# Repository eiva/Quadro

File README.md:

Quadro
======

Собственно это будет клон ардупилота для квадрика.
BOM и прочее будет позднее.
Пока все это теория, т.к. железа у меня нет...

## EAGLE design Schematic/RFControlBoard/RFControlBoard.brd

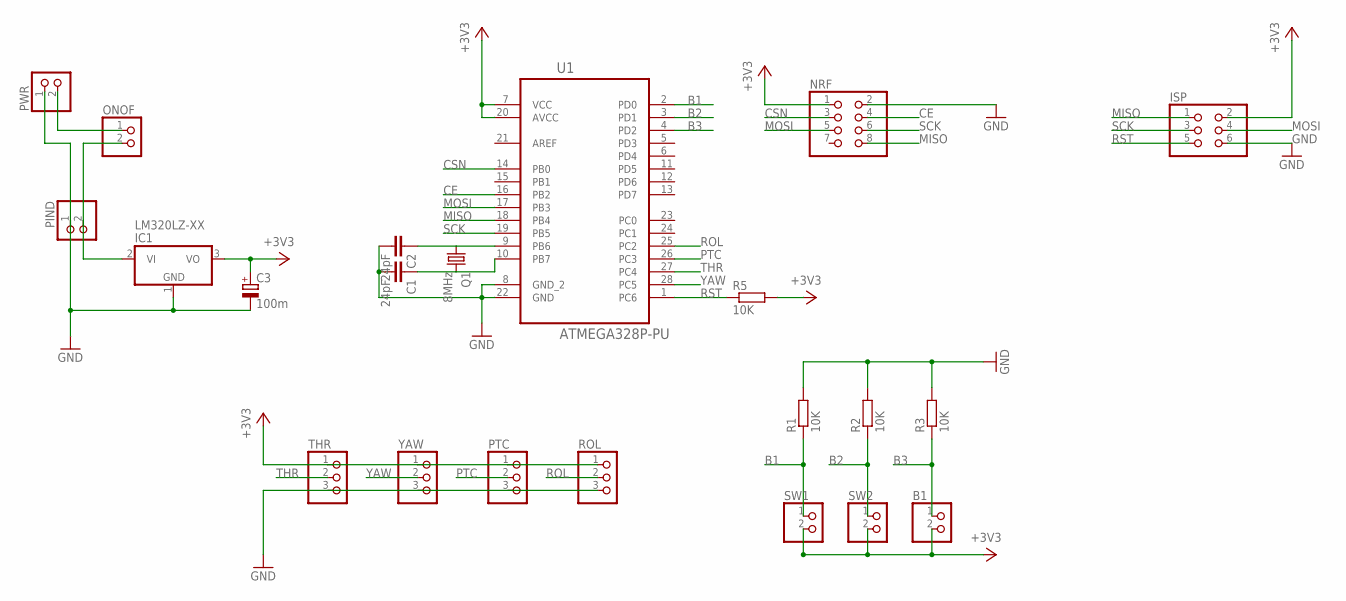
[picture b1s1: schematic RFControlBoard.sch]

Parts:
B1: PINHD-1X2; 1X02
C1, C2: 24pF; C2.5-3
C3: 100m; E2,5-6
IC1: LM320LZ-XX; TO92
ISP: PINHD-2X3; 2X03
NRF: PINHD-2X4; 2X04
ONOF: PINHD-1X2; 1X02
PIND: PINHD-1X2; 1X02
PTC: PINHD-1X3; 1X03
PWR: PINHD-1X2; 1X02
Q1: 8MHz; HC49/S
R1, R2, R3: 10K; 0207/10
R5: 10K; 0207/15
ROL: PINHD-1X3; 1X03
SW1, SW2: PINHD-1X2; 1X02
THR: PINHD-1X3; 1X03
U1: ATMEGA328P-PU; DIP254P762X457-28
YAW: PINHD-1X3; 1X03

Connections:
+3V3: B1.2, C3.+, IC1.3 (VO), ISP.2, NRF.1, PTC.1, R5.2, ROL.1, SW1.2, SW2.2, THR.1, U1.7 (VCC), U1.20 (AVCC), YAW.1
B1: R1.1, SW1.1, U1.2 (PD0)
B2: R2.1, SW2.1, U1.3 (PD1)
B3: B1.1, R3.1, U1.4 (PD2)
CE: NRF.4, U1.16 (PB2)
CSN: NRF.3, U1.14 (PB0)
GND: C1.2, C2.2, C3.-, IC1.1 (GND), ISP.6, NRF.2, PIND.1, PTC.3, PWR.1, R1.2, R2.2, R3.2, ROL.3, THR.3, U1.8 (GND_2), U1.22 (GND), YAW.3
MISO: ISP.1, NRF.8, U1.18 (PB4)
MOSI: ISP.4, NRF.5, U1.17 (PB3)
unnamed: ONOF.1, PWR.2
unnamed: C2.1, Q1.1, U1.9 (PB6)
unnamed: IC1.2 (VI), ONOF.2, PIND.2
unnamed: C1.1, Q1.2, U1.10 (PB7)
PTC: PTC.2, U1.26 (PC3)
ROL: ROL.2, U1.25 (PC2)
RST: ISP.5, R5.1, U1.1 (PC6)
SCK: ISP.3, NRF.6, U1.19 (PB5)
THR: THR.2, U1.27 (PC4)
YAW: U1.28 (PC5), YAW.2

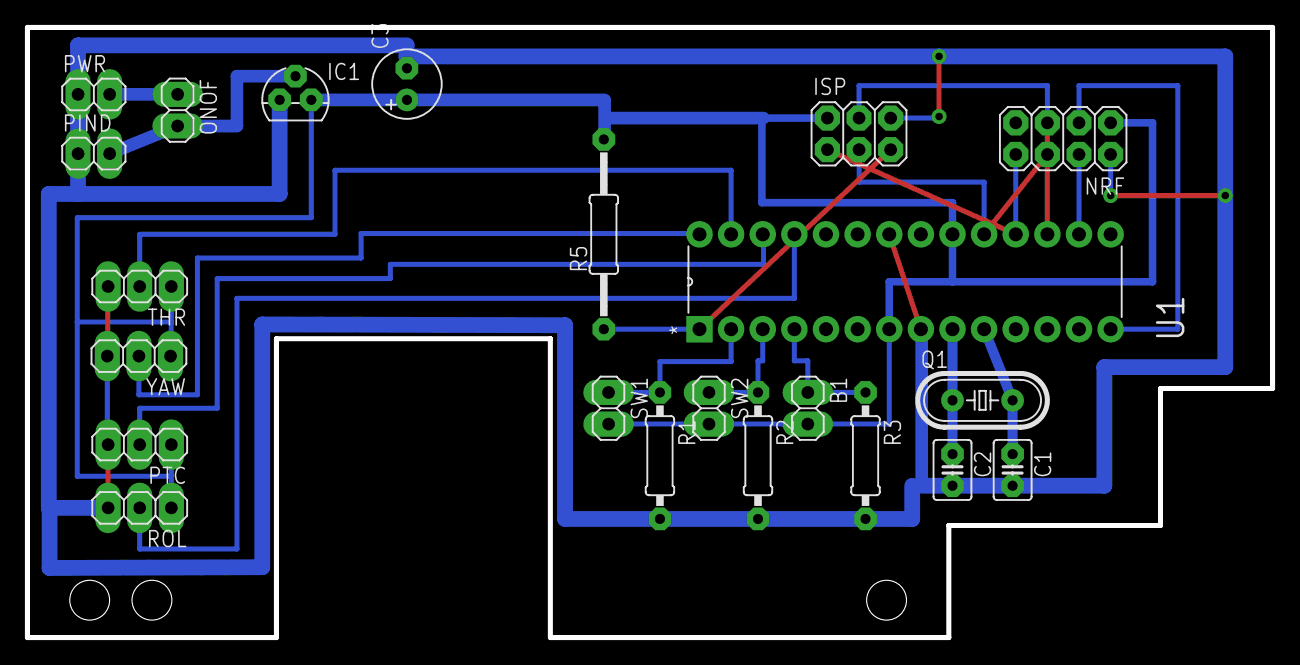
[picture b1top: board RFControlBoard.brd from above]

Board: 2 copper layers, 100.0 x 49.0 mm, 22 parts (0 on the bottom side), 19 nets.

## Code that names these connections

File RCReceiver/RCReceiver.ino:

/**
 * A Mirf example to test the latency between two Ardunio.
 *
 * Pins:
 * Hardware SPI:
 * MISO -> 12
 * MOSI -> 11
 * SCK -> 13
 *
 * Configurable:
 * CE -> 8
 * CSN -> 7
 *
 * Note: To see best case latency comment out all Serial.println
 * statements not displaying the result and load 
 * 'ping_server_interupt' on the server.
 */


#include <SPI.h>
#include <Mirf.h>
#include <nRF24L01.h>
#include <MirfHardwareSpiDriver.h>

#pragma pack(push,1)

struct Packet
{
  uint16_t THR:10;
  uint16_t YAW:10;
  uint16_t PTC:10;
  uint16_t ROL:10;
  uint8_t BT1:1;
  uint8_t BT2:1;
  uint8_t BT3:1;
  uint8_t REST:5;
};

#pragma pack(pop)


//////////////////////CONFIGURATION///////////////////////////////
#define chanel_number 8  //set the number of chanels

#define PPM_FrLen 22500  //set the PPM frame length in microseconds (1ms = 1000µs)
#define PPM_PulseLen 300  //set the pulse length
#define onState 1  //set polarity of the pulses: 1 is positive, 0 is negative
#define sigPin 5  //set PPM signal output pin on the arduino

#define default_servo_value 1500  //set the default servo value
#define  SigMin  1000 // Min value for signal
#define SigMax  2000 // Max value for signal
//////////////////////////////////////////////////////////////////

 
/*this array holds the servo values for the ppm signal
 change theese values in your code (usually servo values move between 1000 and 2000)*/
int ppm[chanel_number];

union PacketSerializer
{
  Packet data;
  uint8_t serialized[6];
};

// Address of reciever.
byte addr[]={0xDB,0xDB,0xDB,0xDB,0xDB};

PacketSerializer packet;


void setup(){

  /*
   * Setup pins / SPI.
   */
   
  /* To change CE / CSN Pins:
   * 
   * Mirf.csnPin = 9;
   * Mirf.cePin = 7;
   */
  /*
  Mirf.cePin = 7;
  Mirf.csnPin = 8;
  */
  Mirf.spi = &MirfHardwareSpi;
  Mirf.init();
  
  /*
   * Configure reciving address.
   */
   
  Mirf.setRADDR(addr);
  
  /*
   * Set the payload length to sizeof(unsigned long) the
   * return type of millis().
   *
   * NB: payload on client and server must be the same.
   */
   
  Mirf.payload = 6;
  
  /*
   * Write channel and payload config then power up reciver.
   */
   
  /*
   * To change channel:
   * 
   * Mirf.channel = 10;
   *
   * NB: Make sure channel is legal in your area.
   */
  Mirf.channel = 10; 
  Mirf.config();
  /*
  _thr.attach(3);
  _yaw.attach(5);
  _pitch.attach(6);
  _roll.attach(9);
  
  _thr.write(0);
  _yaw.write(0);
  _pitch.write(0);
  _roll.write(0);
  
  Serial.println("Beginning ... "); 
  */
  
    //initiallize default ppm values
  for(int i=0; i<chanel_number; i++){
    ppm[i]= default_servo_value;
  }
  ppm[0] = SigMin; // Throttle = 0;

  pinMode(sigPin, OUTPUT);
  digitalWrite(sigPin, !onState);  //set the PPM signal pin to the default state (off)
  
  cli();
  TCCR1A = 0; // set entire TCCR1 register to 0
  TCCR1B = 0;
  
  OCR1A = 100;  // compare match register, change this
  TCCR1B |= (1 << WGM12);  // turn on CTC mode
  TCCR1B |= (1 << CS11);  // 8 prescaler: 0,5 microseconds at 16mhz
  TIMSK1 |= (1 << OCIE1A); // enable timer compare interrupt
  sei();
}

const int THR = 2;
const int YAW = 3;
const int PTC = 1;
const int ROL = 0;
const int BT1 = 4;
const int BT2 = 5;
const int BT3 = 6;

void loop(){
  unsigned long time = millis();

  delay(10);

  while(!Mirf.dataReady()){
    //Serial.println("Waiting");
    if ( ( millis() - time ) > 1000 ) {
      //Serial.println("Timeout on response from server!");
      //_thr.write(_min);
      ppm[THR] = 0; // How to enable failover?
      return;
    }
  }
  
  Mirf.getData((byte *)packet.serialized);
  
  ppm[THR] = map(packet.data.THR,0,1024,SigMin,SigMax);
  ppm[YAW] = map(packet.data.YAW,0,1024,SigMin,SigMax+300);  
  ppm[PTC] = map(packet.data.PTC,0,1024,SigMin,SigMax);
  ppm[ROL] = map(packet.data.ROL,0,1024,SigMin,SigMax);
  ppm[BT1] = packet.data.BT1?SigMax:SigMin;
  ppm[BT2] = packet.data.BT2?SigMax:SigMin;
  ppm[BT3] = packet.data.BT3?SigMax:SigMin;
  
/*
  _thr.write(  map(packet.data.THR,0,1024,_min,_max));
  _yaw.write(  map(packet.data.YAW,0,1024,_min,_max));  
  _pitch.write(map(packet.data.PTC,0,1024,_min,_max));
  _roll.write( map(packet.data.ROL,0,1024,_min,_max));
  */
  //Serial.print(".");
} 
  
ISR(TIMER1_COMPA_vect){  //leave this alone
  static boolean state = true;
  
  TCNT1 = 0;
  
  if(state) {  //start pulse
    digitalWrite(sigPin, onState);
    OCR1A = PPM_PulseLen * 2;
    state = false;
  }
  else{  //end pulse and calculate when to start the next pulse
    static byte cur_chan_numb;
    static unsigned int calc_rest;
  
    digitalWrite(sigPin, !onState);
    state = true;

    if(cur_chan_numb >= chanel_number){
      cur_chan_numb = 0;
      calc_rest = calc_rest + PPM_PulseLen;// 
      OCR1A = (PPM_FrLen - calc_rest) * 2;
      calc_rest = 0;
    }
    else{
      OCR1A = (ppm[cur_chan_numb] - PPM_PulseLen) * 2;
      calc_rest = calc_rest + ppm[cur_chan_numb];
      cur_chan_numb++;
    }     
  }
}

  

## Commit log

2014-05-10 Dummy STM32 project for QuadroControlBoard
2014-05-10 Dummy project for RCVontrol ATMEGA328P board. Based on arduino.
2014-05-10 Structure update
2014-05-10 Thanks to https://github.com/LonelyWolf/stm32/blob/master/Nrf24l01 I got RF implementation from here.
2014-05-13 Test ping
2014-05-17 Trajectory estimation
2014-05-17 Ignore matlab intermediate
2014-05-21 Semihosting now works. nrf24 still not....
2014-05-22 Setup RF configuration to be compartable with mirf Arduino library.
2014-05-22 Several filters test. Seems Im doing something wrong: it all has ugly accuracy.
2014-05-22 Change address accoding to LSB MSB safety. Test for receiver.
2014-06-01 Now its really works. Itested. Need to check: does it really work if no data transmitted.
2014-06-11 Заработали прерывания и прочее
2014-06-29 RF control board schematic
2014-06-29 Разведено для однослойной платы + пары проводков.
2014-07-03 RC Control board (RCCB): 1) Schematic is updated for laser ironing PCB production :) 2) Initial version of RCCB firmware (3.3v 8Mhz). not tested.
2014-07-08 Final version of RCControl Test utility for ESC test. Initial commit for TestReciever - all tests. Need to migrate to stm32.
2014-07-12 Draft simplest quadro firmware implementation.
2014-07-14 Correct init, calibrate and arm procedures.
2014-07-15 First ground off. Stabilizer is not work.
2014-07-15 Move file
2014-07-15 Test IMU modules
2014-07-15 A bit.
2014-07-16 Calibrated broken ADXL345 accelerometer. (it have so huge offset in measurement)...
2014-07-16 Complimentary filter for stabilizer are used. Now drift on pitch/roll a really small, but still have small offset on relaxed state. Need to find how to auto calibrate IMU.
2014-07-17 First flight like a fault: from stand to crush.... Whats wrong? One thing: engine power control. 1) Need to build safe frame. 2) Need to check engine power.
2014-07-26 Temporary disable acc control.
2014-07-26 Add all side libs to make it buildable by clean arduino IDE install.
2014-07-27 Continue splitting super file to small ones. Fix issue with compilation in ubuntu. Im too lazzy tomake real work now. Quadro is still not fly, and it is totally unpredicted motor activity.
2014-07-27 Next part of files.
2014-07-27 At last - all ino file splitted. Compilation checked.
2014-07-28 OpenIMU added to the project.
2014-08-06 Serial Listener
2014-08-10 Port helper. LedInfo ported. Delay function. TESTED
2014-08-12 STM32 PWM Servo control. Motors class for ESC motor driving at 50Hz.
2014-08-13 Add ADC support to the project. Test for Servo position in respect for resistor position.
2014-08-13 HAL for SPI. Prepare for nRF integration.
2014-08-14 Some additional SPI stuff and nRF initialization intro.
2014-08-15 nRF24 initial routines...
2014-08-15 Some helper stuff.
2014-08-15 End of development. Device dont fit.
2014-08-15 Decorations... Still dont works.
2014-08-16 Introduced RadioLink class.
2014-08-16 Still want work...
2014-08-17 Now it is connected to RCControlBoard. 2.4Ghz channel 10. Test passed.
2014-08-17 Some small re-placements.
2014-08-17 Time routines.
2014-08-17 Compilation fixes.
2014-08-17 Vector implementation.
2014-08-17 Some skeletons and refactorings.
2014-08-18 Some additional stab stuff.
2014-08-22 mpu9250 initial version of IMU ussages.
2014-08-25 Stm32 USB HID initial project.
2014-08-25 Flight controller mpu9250 initial support.
2014-08-25 Some dirty stuff.
2014-08-25 Other stuff.
2014-08-26 Simple HID device protocol implementation.
2014-08-27 New part.
2014-08-27 Sub module added
2014-08-27 Simple WPF app
2014-08-27 Solution
2014-08-28 FlightMonitor Protocol intro
2014-09-03 USB Protocol
2014-09-03 USB HID communication.
2014-09-03 USB connection
2014-09-03 F4 FREERTOS test
2014-09-03 Some tests + PWM
2014-09-04 STM32F4 seems to be broken: SDIO dont work on my chip.
2014-09-04 SDIO init passed.
2014-09-05 Commit 1 inside simplification.
2014-09-05 Commit 2 in re-factoring. SD_Init now passes with all SD_OK results.
2014-09-05 Now works but only if fmt created by fsfat... No any other possibilities. Win8 dont recognize SD after this.
2014-09-06 Write operation is now wait for completion of fifo.
2014-09-06 STM32F4 SMDIO SD in push-pull mode with fatfs is now works!
2014-09-07 SPI initialization.
2014-09-08 Spi now works with stm32f4. NRF ping ok!
2014-09-08 nrf link test done.
2014-09-09 RTOS structure initialization. Motors initial stuff.
2014-09-12 Some other stuff for RTOS. Switched to C++ constructioin. Change signatures from & to *.
2014-09-14 - C++ overhead optimizations. - Logger class. - NOT works: flash loses all data due to unsynchronized access. - Fix in ff.h file for better c++ compatibility. - all general includes moved to conf fil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
2014-09-14 - different handlers for several fault-ISRs - Log now works (but with some periodical crap... still need to be investigated... - ready for IMU... (but still don't have one)
2014-09-14 - AHRS added. - IMUProcessor task introduced. - AHRS added to this task. - Log extended.
2014-09-14 Renamed.
2014-09-14 Renamed
2014-09-14 - Clean
2014-09-14 - renamed
2014-09-14 Clean and ready for development.
2014-09-16 MPU9250 added to project
2014-09-19 - USART tested - System core clock adjusted to board 8MHz HSE. TODO: Test PWM, SPI for speed condition.
2014-09-19 - MAVLink added to project... - try to add parameters lib.
2014-09-20 Added AHRS and MAVLink reporting. Thats works.
2014-09-21 - Added sensor data to telemetry. - Fixed issue with wrong gyro processing. - Prepering to use magnetometer.
2014-09-21 - magnetometer - rc telemetry.
2014-09-22 - Quaternion to Euler transformation. - Telemetry switched to Euler.
2014-09-25 - Parameters protocol - RC parameters - RC calibration
2014-09-25 - scaled telemetry -- scaleing dont work.
2014-09-25 - RF sticks calibration, and initial parameters.
2014-09-26 - Fixed issue with Euler angles. - Extracted Commander task. - Added PID object to control attitude. - Fixed issue with wrong PWM prescaller. DONT WORK.
2014-09-27 - basic motor thrust distribution. - still dont work: need to calibrate parameters.
2014-10-03 Extracts motor control logic from commander task.
2014-10-11 Switch to 400Hz pwm. Added ESC arming.
2014-10-12 Prepare to eeprom support
2014-10-12 add eeprom lib
2014-10-19 Low pass filter for filter noise from IMU. eeprom emulation. NOT WORK
2014-12-14 RC receiver (nRF->4xPWM), tested on APM.
2014-12-29 nRF->PPM encoder.
2014-12-29 Проверка моторов.
